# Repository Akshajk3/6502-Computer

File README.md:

# W65C816S Computer

**A homebrew 8/16-bit computer built around the W65C816S processor, along with the custom PCBs and tools needed to program and debug it.**

**EEPROM Programmer:**

**Debug Board:**

This project is about understanding a computer from the transistor-level chips up: no operating system, no microcontroller doing the work behind the scenes, just a CPU, memory, and I/O wired together on a shared bus and running machine code I write and flash myself.

Along the way, I've designed two printed circuit boards in KiCad, written firmware and Python tools to program the system's ROM, and rebuilt the EEPROM programmer three times on three different platforms as I ran into hardware limits.

---

## Why the W65C816S?

The repo is named after the 6502, the processor inside the Apple II, Commodore 64, and NES. The computer actually uses the **W65C816S**, a modern descendant of the 6502 (and the CPU family used in the Super Nintendo and Apple IIGS).

The 65C816 boots in a 6502 **emulation mode**, so it runs ordinary 6502 code, but it can switch into a **native mode** with 16-bit registers and a 24-bit address space (16 MB instead of 64 KB). That gives the project room to grow beyond a classic 6502 build later on.

---

## System design

The computer is made of four main chips connected over a shared address and data bus:

| Chip | Part | Role |
|------|------|------|
| CPU | WDC W65C816S | 8/16-bit processor |
| ROM | 28C256 | 32 KB EEPROM that holds the program |
| RAM | CY62256 | 32 KB static RAM |
| I/O | WDC W65C22 | Versatile Interface Adapter (VIA): parallel I/O ports and timers |

```mermaid
flowchart LR
    CPU["W65C816S<br/>CPU"]
    ROM["28C256<br/>32 KB EEPROM"]
    RAM["CY62256<br/>32 KB SRAM"]
    VIA["W65C22<br/>VIA"]
    IO["LEDs / peripherals"]

    CPU <== "Address bus A0–A15<br/>Data bus D0–D7" ==> ROM
    CPU <==> RAM
    CPU <==> VIA
    VIA --> IO
```

### Memory map (so far)

| Address range | Device |
|---------------|--------|
| `$6000` – `$600F` | W65C22 VIA registers (`$6000` = Port B, `$6002` = Port B direction) |
| `$8000` – `$FFFF` | 28C256 ROM |
| `$FFFC` – `$FFFD` | Reset vector (where the CPU starts executing) |

---

## Hardware

### 1. CPU debug board

**Files:** `6502 Computer.kicad_sch`, `6502 Computer.kicad_pcb`, `production/`

A PCB that holds the W65C816S in a 40-pin socket and breaks out every useful signal to labeled pin headers so the CPU can be probed and monitored:

- **16-pin header:** address bus A0–A15
- **8-pin header:** data bus D0–D7
- **Control headers:** CLK, R/W, E, MX, VDA, VPA, VP, and ML
- **Power header:** 5V and GND
- **Reset circuit:** push button with a 10 kΩ pull-up and 1 µF capacitor, so the CPU gets a clean reset pulse
- **Pull-up resistors (3.3 kΩ)** on the RDY, IRQ, and NMI inputs, so the CPU doesn't halt or take spurious interrupts while those lines are unused

All the signal names are printed on the silkscreen next to each pin.

### 2. Arduino Mega bus monitor

**Files:** `W65C816S_monitor/W65C816S_monitor.ino`

The debug board is paired with an Arduino Mega that acts as both the **clock** and a **logic analyzer**. The Mega drives the CPU's clock pin itself at a very slow speed (about 50 Hz) and, on every clock cycle, reads all 16 address lines, all 8 data lines, and the R/W line, then prints them over serial. Example output:

```
1111111111111100  00000000   fffc  r  00
1111111111111101  00000000   fffd  r  80
1000000000000000  10101001   8000  r  a9
```

This makes it possible to watch the CPU fetch its reset vector and step through a program one bus cycle at a time, which is how I verify the hardware is wired correctly before running it at full speed.

### 3. EEPROM programmer

**Files:** `EEPROM_Programmer/`

The ROM chip has to be loaded with a program before the computer can run, so I built a dedicated programmer for the 28C256. It went through three versions:

| Version | Platform | Outcome |
|---------|----------|---------|
| 1 | Arduino Uno | Worked, but the Uno doesn't have enough GPIO pins, so only 128 bytes of the 32 KB chip were reachable |
| 2 | Raspberry Pi (`file_uploader.py`) | Full 32 KB address range driven directly from the Pi's GPIO pins; can flash complete ROM images |
| 3 | Arduino Mega shield (PCB) | A custom shield that plugs onto a Mega and holds the EEPROM in a socket, wiring all 15 address lines, 8 data lines, and the control lines straight to the Mega's pins |

The Raspberry Pi tool (`file_uploader.py`) has two modes:

- **ROM flashing:** `python3 file_uploader.py rom.bin` writes a full binary to the chip, verifies every byte by reading it back, and automatically retries any addresses that failed.
- **Interactive monitor:** a small BIOS-style prompt for working with the chip by hand:

```
Enter command (clear/write/read <address> <data>/exit): write 0000 a9
Writing 0xA9 to address 0x00
Enter command (clear/write/read <address> <data>/exit): read 0000
Read 0xA9 from address 0x0000
```

Each write uses **data polling**: after writing a byte, the programmer keeps reading that address until the chip returns the correct value, since the EEPROM needs a few milliseconds to finish storing each byte internally.

---

## Software

### Writing programs

Programs are written in 6502 assembly. For example, `EEPROM_Programmer/blink.s` sets the VIA's Port B to output and writes a pattern to it to light LEDs (slightly simplified):

```asm
    .org $8000

reset:
    lda #$ff
    sta $6002     ; set all Port B pins to output

loop:
    lda #$aa
    sta $6000     ; write 10101010 to Port B
    jmp loop

    .org $fffc
    .word reset   ; reset vector points to the start of the program
    .word $0000
```

### Build and flash

1. Assemble the program into a 32 KB binary (for example with [vasm](http://sun.hasenbraten.de/vasm/)):
   ```bash
   vasm6502_oldstyle -Fbin -dotdir blink.s -o rom.bin
   ```
2. Copy `rom.bin` to the Raspberry Pi and flash it:
   ```bash
   python3 file_uploader.py rom.bin
   ```
3. Move the EEPROM into the computer and press reset.

`makerom.py` generates a test ROM filled entirely with `$EA` (the 6502 `NOP` instruction). This is useful for a first power-on, since the CPU just walks through memory and the address bus counts upward on the monitor.

`serial_monitor.py` is a small two-way serial terminal for talking to the Arduino-based tools from a computer.

---

## Repository layout

```
6502-Computer/
├── 6502 Computer.kicad_*        # CPU debug board (schematic + PCB)
├── 6502_computer.kicad_sch      # Full system schematic: CPU, ROM, RAM, VIA
├── clock.kicad_sch              # Clock module (not started)
├── production/                  # Gerbers, BOM, and placement files for the debug board
├── W65C816S_monitor/            # Arduino Mega bus monitor / clock
├── EEPROM_Programmer/
│   ├── EEPROM_Programmer.kicad_*    # Arduino Mega programmer shield
│   ├── production/                  # Manufacturing files for the shield
│   ├── EEPROM_Programmer.ino        # Mega firmware (in progress)
│   ├── file_uploader.py             # Raspberry Pi programmer and ROM flasher
│   ├── makerom.py                   # Generates a NOP-filled test ROM
│   ├── serial_monitor.py            # Serial terminal
│   └── blink.s, test.s              # Example assembly programs
└── Assembly Code/
```

---

## Project status

| Part | Status |
|------|--------|
| CPU debug board | PCB designed and sent for manufacturing |
| Bus monitor firmware | Working |
| EEPROM programmer (Raspberry Pi) | Working: reads, writes, clears, and flashes full ROM images |
| EEPROM programmer shield (Arduino Mega) | PCB designed and sent for manufacturing; firmware being ported from the Pi version |
| Full system schematic (CPU + ROM + RAM + VIA) | Schematic drawn; address decoding and PCB layout still to do |
| Clock module | Planned |

## Roadmap

- [ ] Finish the Arduino Mega programmer firmware
- [ ] Assemble and test both PCBs when they arrive
- [ ] Finalize address decoding and lay out the full computer PCB
- [ ] Add a dedicated clock module (adjustable speed plus single-step)
- [ ] Add an LCD display and a serial port for input/output
- [ ] Latch the bank address byte to use the 65C816's full 24-bit address space

---

## Tools

KiCad · Arduino (C++) · Python · Raspberry Pi GPIO · 6502 assembly

## Acknowledgments
 
This project was inspired by Ben Eater's [**"Build a 6502 computer"**](https://eater.net/6502) video series, which is where I learned how microprocessors work: how a CPU fetches instructions, how it talks to memory and I/O over the address and data buses, and how a computer starts up from its reset vector.
 
The hardware in this repo is my own work. I chose to build around the W65C816S instead of the 6502, and I did all the wiring and designed both PCBs (the CPU debug board and the Arduino Mega EEPROM programmer shield) myself, along with the Raspberry Pi EEPROM programmer.
 
The Arduino bus monitor sketch and the example assembly programs are based on the ones shown in the series.

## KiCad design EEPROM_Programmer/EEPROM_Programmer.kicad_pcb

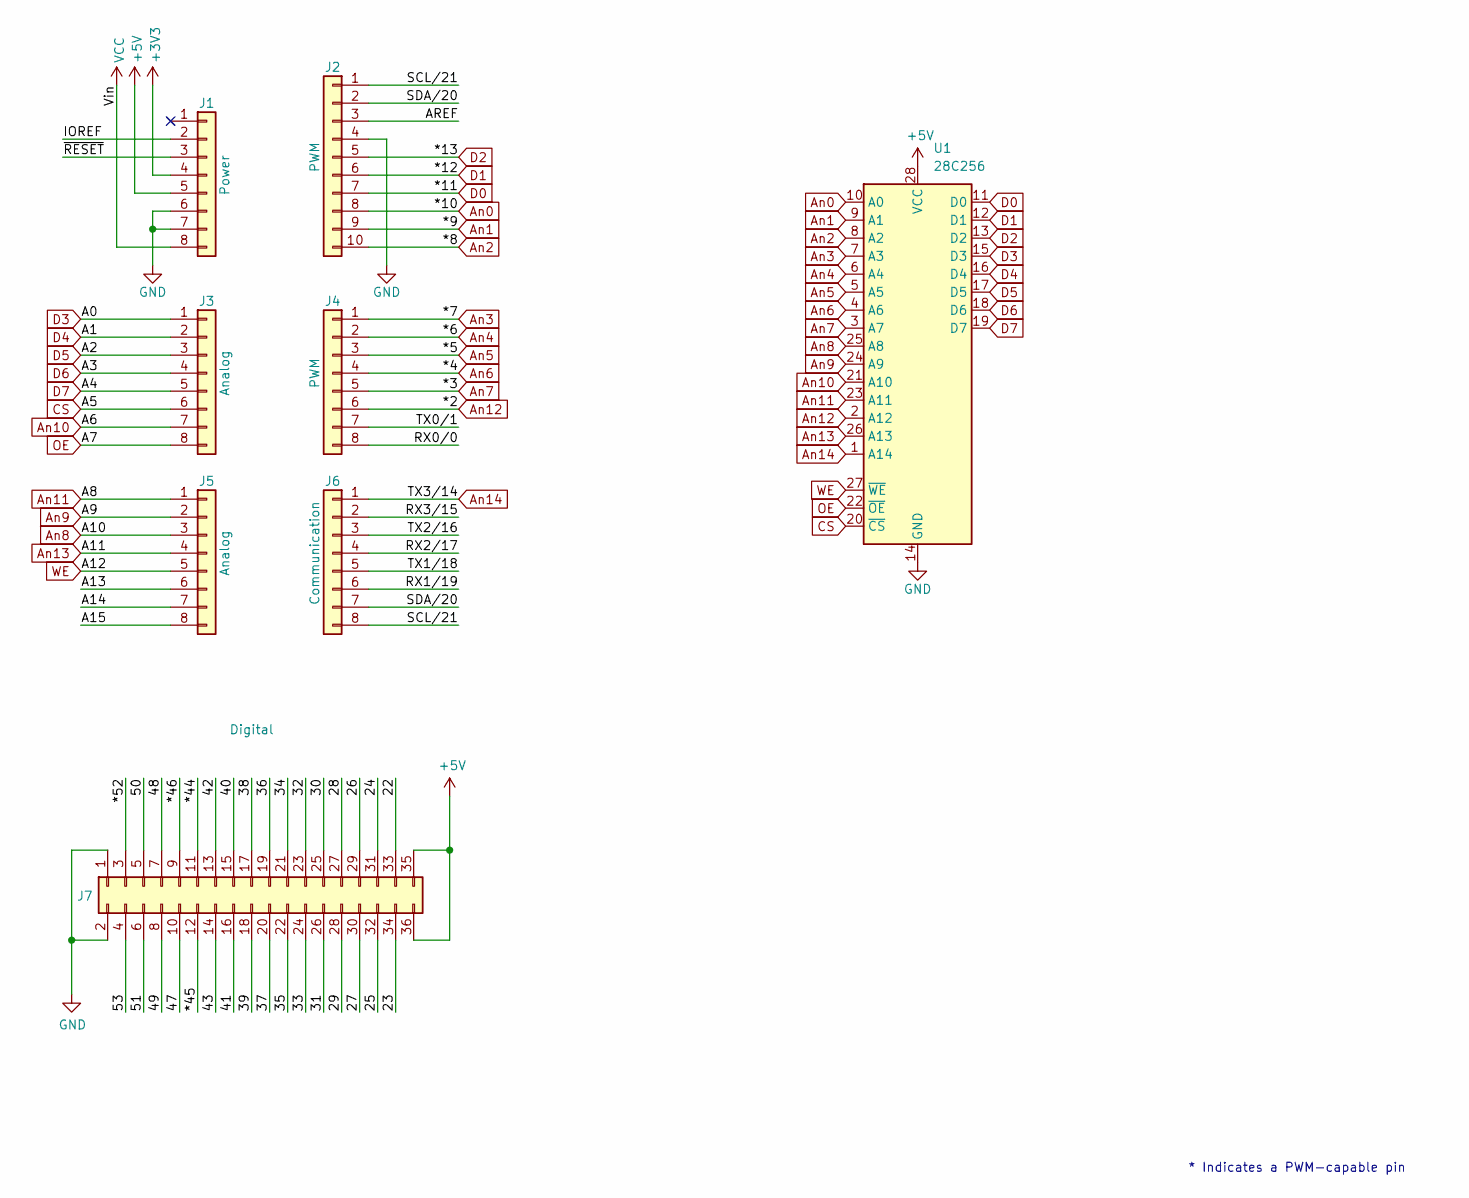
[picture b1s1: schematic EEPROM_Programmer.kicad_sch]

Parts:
J1: Power; PinHeader_1x08_P2.54mm_Vertical
J2: PWM; PinHeader_1x10_P2.54mm_Vertical
J3, J5: Analog; PinHeader_1x08_P2.54mm_Vertical
J4: PWM; PinHeader_1x08_P2.54mm_Vertical
J6: Communication; PinHeader_1x08_P2.54mm_Vertical
J7: Digital; PinHeader_2x18_P2.54mm_Vertical
U1: 28C256; DIP-28_W15.24mm_Socket

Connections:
+3V3: J1.4
+5V: J1.5, J7.35, J7.36, U1.28 (VCC)
/22: J7.33
/23: J7.34
/24: J7.31
/25: J7.32
/26: J7.29
/27: J7.30
/28: J7.27
/29: J7.28
/30: J7.25
/31: J7.26
/32: J7.23
/33: J7.24
/34: J7.21
/35: J7.22
/36: J7.19
/37: J7.20
/38: J7.17
/39: J7.18
/40: J7.15
/41: J7.16
/42: J7.13
/43: J7.14
/47: J7.10
/48: J7.7
/49: J7.8
/50: J7.5
/51: J7.6
/53: J7.4
/*44: J7.11
/*45: J7.12
/*46: J7.9
/*52: J7.3
/A13: J5.6
/A14: J5.7
/A15: J5.8
/AREF: J2.3
/IOREF: J1.2
/RX0/0: J4.8
/RX1/19: J6.6
/RX2/17: J6.4
/RX3/15: J6.2
/SCL/21: J2.1, J6.8
/SDA/20: J2.2, J6.7
/TX0/1: J4.7
/TX1/18: J6.5
/TX2/16: J6.3
/~RESET: J1.3
An0: J2.8, U1.10 (A0)
An1: J2.9, U1.9 (A1)
An2: J2.10, U1.8 (A2)
An3: J4.1, U1.7 (A3)
An4: J4.2, U1.6 (A4)
An5: J4.3, U1.5 (A5)
An6: J4.4, U1.4 (A6)
An7: J4.5, U1.3 (A7)
An8: J5.3, U1.25 (A8)
An9: J5.2, U1.24 (A9)
An10: J3.7, U1.21 (A10)
An11: J5.1, U1.23 (A11)
An12: J4.6, U1.2 (A12)
An13: J5.4, U1.26 (A13)
An14: J6.1, U1.1 (A14)
CS: J3.6, U1.20 (~CS)
D0: J2.7, U1.11 (D0)
D1: J2.6, U1.12 (D1)
D2: J2.5, U1.13 (D2)
D3: J3.1, U1.15 (D3)
D4: J3.2, U1.16 (D4)
D5: J3.3, U1.17 (D5)
D6: J3.4, U1.18 (D6)
D7: J3.5, U1.19 (D7)
GND: J1.6, J1.7, J2.4, J7.1, J7.2, U1.14 (GND)
OE: J3.8, U1.22 (~OE)
VCC: J1.8
WE: J5.5, U1.27 (~WE)

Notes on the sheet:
* Indicates a PWM-capable pin

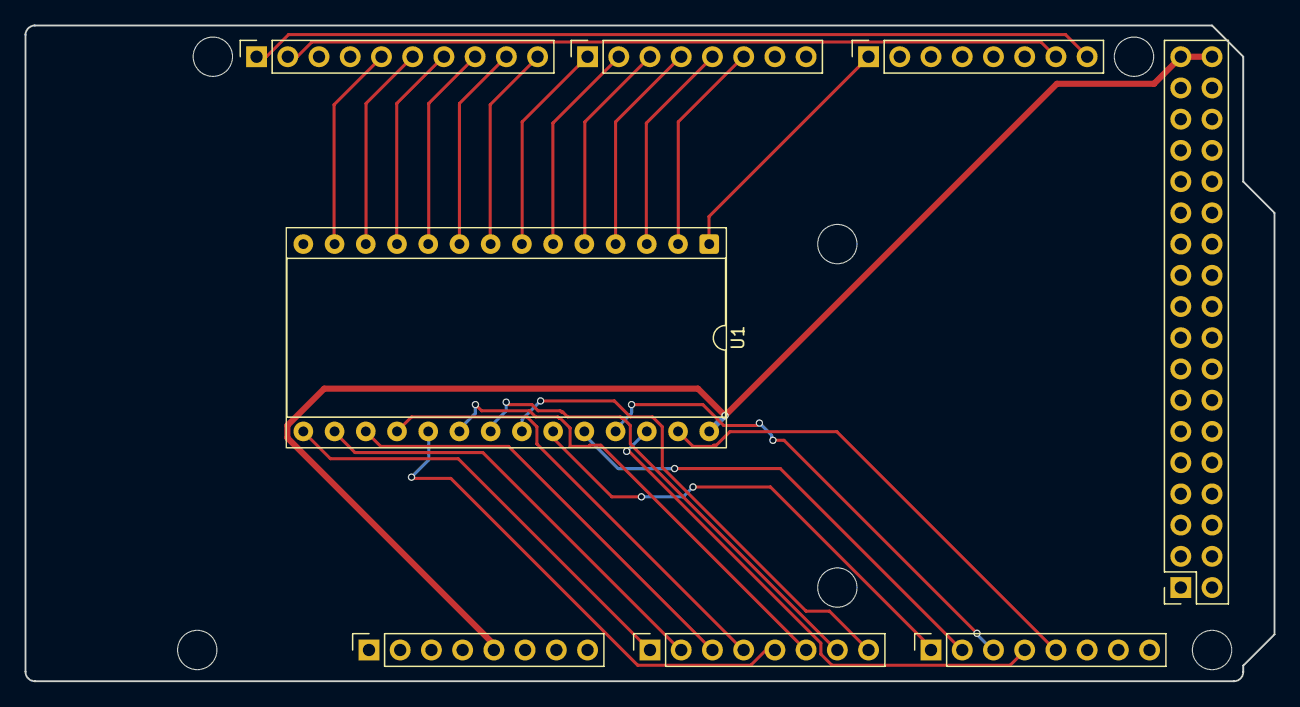
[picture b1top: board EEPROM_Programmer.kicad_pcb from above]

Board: 2 copper layers, 101.6 x 53.3 mm, 14 parts (0 on the bottom side), 30 nets.

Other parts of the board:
MH1, MH2, MH3, MH4, MH5, MH6: MountingHole_3.2mm

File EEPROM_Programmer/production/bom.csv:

Designator,Footprint,Quantity,Value,LCSC Part #
J1,PinSocket_1x08_P2.54mm_Vertical,1,Power,
J2,PinSocket_1x10_P2.54mm_Vertical,1,PWM,
"J3, J5",PinSocket_1x08_P2.54mm_Vertical,2,Analog,
J4,PinSocket_1x08_P2.54mm_Vertical,1,PWM,
J6,PinSocket_1x08_P2.54mm_Vertical,1,Communication,
J7,PinSocket_2x18_P2.54mm_Vertical,1,Digital,
U1,DIP-28_W15.24mm_Socket,1,28C256,

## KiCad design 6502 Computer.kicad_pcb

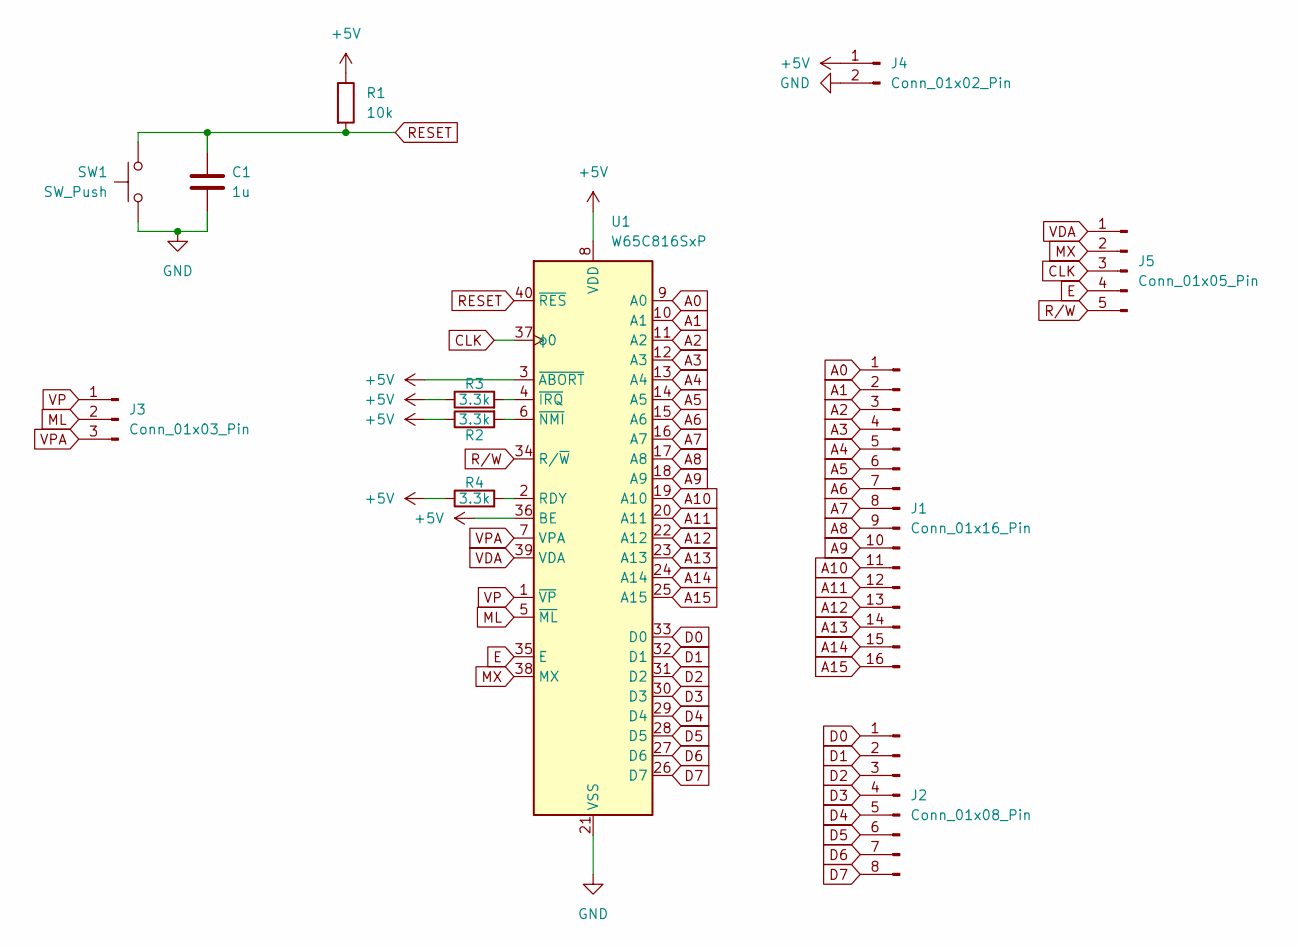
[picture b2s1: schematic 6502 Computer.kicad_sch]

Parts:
C1: 1u; C_Disc_D5.0mm_W2.5mm_P5.00mm
J1: Conn_01x16_Pin; PinHeader_1x16_P2.54mm_Vertical
J2: Conn_01x08_Pin; PinHeader_1x08_P2.54mm_Vertical
J3: Conn_01x03_Pin; PinHeader_1x03_P2.54mm_Vertical
J4: Conn_01x02_Pin; PinHeader_1x02_P2.54mm_Vertical
J5: Conn_01x05_Pin; PinHeader_1x05_P2.54mm_Vertical
R1: 10k; R_Axial_DIN0207_L6.3mm_D2.5mm_P10.16mm_Horizontal
R2, R3, R4: 3.3k; R_Axial_DIN0207_L6.3mm_D2.5mm_P10.16mm_Horizontal
SW1: SW_Push; SW_PUSH_6mm_H5mm
U1: W65C816SxP; DIP-40_W15.24mm_Socket

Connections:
+5V: J4.1, R1.1, R2.1, R3.1, R4.1, U1.3 (~ABORT), U1.8 (VDD), U1.36 (BE)
A0: J1.1, U1.9 (A0)
A1: J1.2, U1.10 (A1)
A2: J1.3, U1.11 (A2)
A3: J1.4, U1.12 (A3)
A4: J1.5, U1.13 (A4)
A5: J1.6, U1.14 (A5)
A6: J1.7, U1.15 (A6)
A7: J1.8, U1.16 (A7)
A8: J1.9, U1.17 (A8)
A9: J1.10, U1.18 (A9)
A10: J1.11, U1.19 (A10)
A11: J1.12, U1.20 (A11)
A12: J1.13, U1.22 (A12)
A13: J1.14, U1.23 (A13)
A14: J1.15, U1.24 (A14)
A15: J1.16, U1.25 (A15)
CLK: J5.3, U1.37 (ϕ0)
D0: J2.1, U1.33 (D0)
D1: J2.2, U1.32 (D1)
D2: J2.3, U1.31 (D2)
D3: J2.4, U1.30 (D3)
D4: J2.5, U1.29 (D4)
D5: J2.6, U1.28 (D5)
D6: J2.7, U1.27 (D6)
D7: J2.8, U1.26 (D7)
E: J5.4, U1.35 (E)
GND: C1.2, J4.2, SW1.2, U1.21 (VSS)
ML: J3.2, U1.5 (~ML)
MX: J5.2, U1.38 (MX)
unnamed: R4.2, U1.2 (RDY)
unnamed: R3.2, U1.4 (~IRQ)
unnamed: R2.2, U1.6 (~NMI)
RESET: C1.1, R1.2, SW1.1, U1.40 (~RES)
R/W: J5.5, U1.34 (R/~W)
VDA: J5.1, U1.39 (VDA)
VP: J3.1, U1.1 (~VP)
VPA: J3.3, U1.7 (VPA)

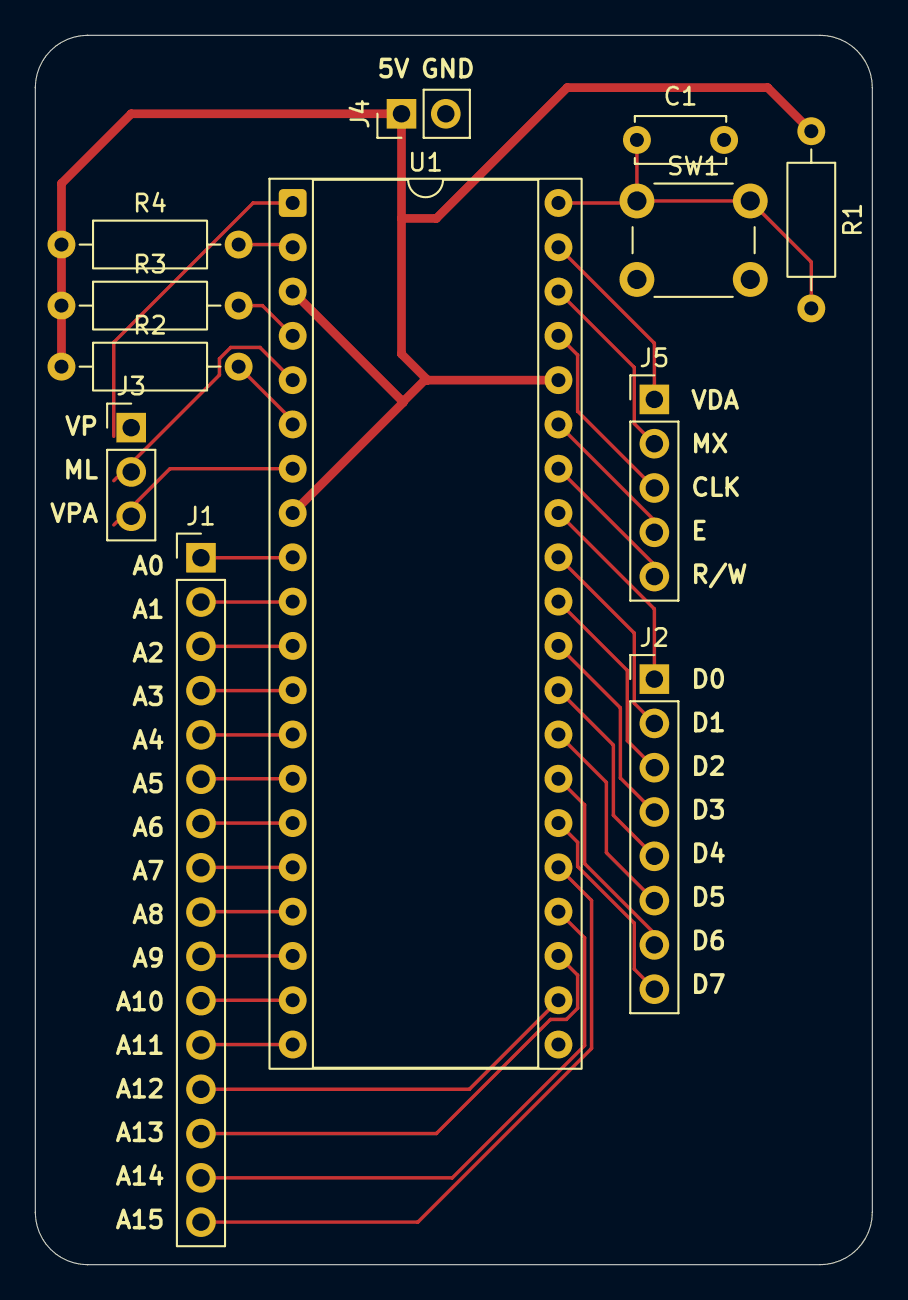
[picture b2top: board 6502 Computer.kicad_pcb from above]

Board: 2 copper layers, 48.0 x 70.5 mm, 12 parts (0 on the bottom side), 38 nets.

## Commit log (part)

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2025-02-17 added EEPROM programmer
2025-02-24 fixed issue with schematics where the wrong CPU was used <:(
2025-05-11 oh yea it works, also supports a super simple BIOS were you can read, write, and clear Values from the EEPROM
2025-05-11 allowed the file uploader to emulate funcitonality of the serial montior, need to reimplement code with a raspberry pi because arduino uno doesnt have enought GPIO pins
2025-05-12 rewrote EEPROM programmer to work with raspberry pi, giving address to full 32k and full addressable range rather than just the 128b with the arduino uno
2025-05-12 wrote a simple assembly program to blink some LED havent tested yet
2025-05-13 wrote some test assembly code
2025-05-14 got the file uploader working, and wrote a script to generate a writable ROM file from a assembled bin file
2025-06-28 started reworking the EERPOM programmer for arduino mega
